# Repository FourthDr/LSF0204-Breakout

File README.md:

LSF0204 Breakout Board
======================

Here are Eagle files for my LSF0204(D) Breakout Board.

<p align="center">
  
</p>

The LSF0204 is a 4-bit, bidirectional, multi-voltage level translator. More info and datasheet here: http://www.ti.com/product/lsf0204

##Features and parts list:

* **U1:** LSF0204(D) IC from Texas Instruments, TSSOP-14 package.
* **C1,C2:** 0.1uF 0805 package. These are decoupling caps.
* **R1-R8:** 4.7k-10k ohm, 0805 package. I2C pull-up resistors for every input/output.
* **R9:** 10k ohm, 0805 package. Pull-down resistor to GND, for LSF0204D: the EN pin is active low.
* **SJ1:** solder jumper to VA, connect for LSF0204 (non-D): the EN pin is active high.

You can visit my website at www.truzzi.me.

Any suggestions or comments are appreciated!

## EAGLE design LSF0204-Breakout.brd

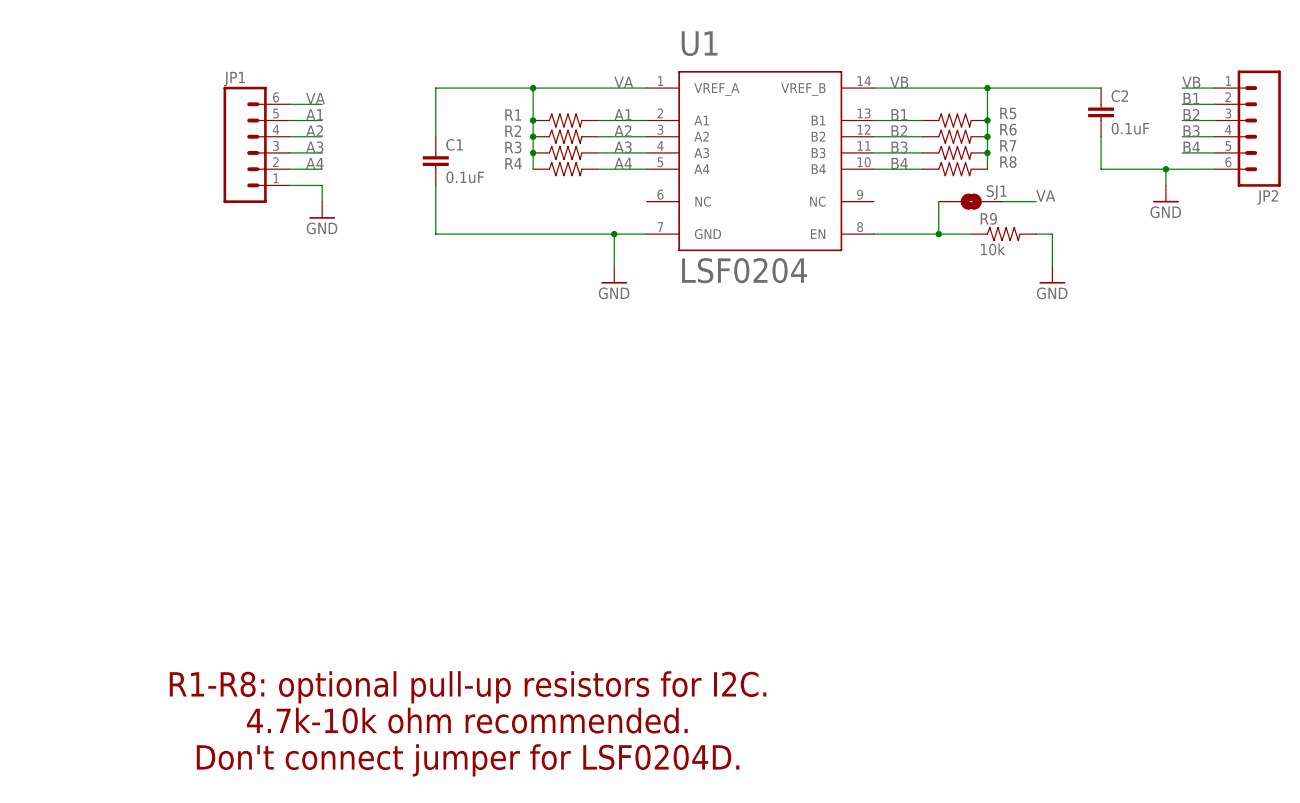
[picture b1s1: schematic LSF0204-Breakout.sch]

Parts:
C1, C2: 0.1uF; 0805
JP1, JP2: M06LOCK; 1X06_LOCK
R1, R2, R3, R4, R5, R6, R7, R8: RESISTOR0805-RES; 0805
R9: 10k; 0805
SJ1: JUMPER-PAD-2-NO; PAD-JUMPER-2-NO_NO_SILK
U1: LSF0204; TSSOP_14

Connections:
A1: JP1.5, R1.2, U1.2 (A1)
A2: JP1.4, R2.2, U1.3 (A2)
A3: JP1.3, R3.2, U1.4 (A3)
A4: JP1.2, R4.2, U1.5 (A4)
B1: JP2.2, R5.1, U1.13 (B1)
B2: JP2.3, R6.1, U1.12 (B2)
B3: JP2.4, R7.1, U1.11 (B3)
B4: JP2.5, R8.1, U1.10 (B4)
GND: C1.2, C2.2, JP1.1, JP2.6, R9.2, U1.7 (GND)
unnamed: R9.1, SJ1.1, U1.8 (EN)
VA: C1.1, JP1.6, R1.1, R2.1, R3.1, R4.1, SJ1.2, U1.1 (VREF_A)
VB: C2.1, JP2.1, R5.2, R6.2, R7.2, R8.2, U1.14 (VREF_B)

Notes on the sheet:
R1-R8: optional pull-up resistors for I2C. 4.7k-10k ohm recommended. Don't connect jumper for LSF0204D.

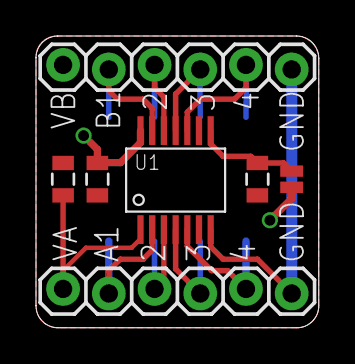
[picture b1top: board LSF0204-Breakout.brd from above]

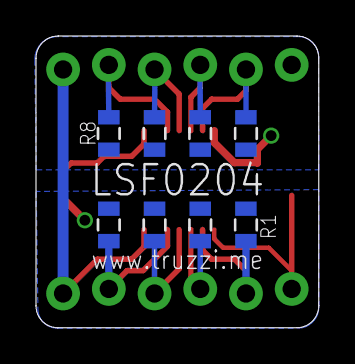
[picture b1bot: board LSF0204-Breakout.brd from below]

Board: 2 copper layers, 15.7 x 16.2 mm, 15 parts (8 on the bottom side), 12 nets.

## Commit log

2015-01-30 :tada: Added .gitattributes & .gitignore files
2015-01-30 Initial release of BRD and SCH files.
2015-01-30 Updated schematics and aesthetics.
2015-01-30 README file created.
2015-01-30 Fixed resistor markings, added image
2015-01-30 New picture

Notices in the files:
LSF0204-Breakout.sch:
LICENSE: Released under CC BY-NC-SA 4.0
parts and their libraries:
SparkFun-Passives: Licensing: Creative Commons ShareAlike 4.0 International - https://creativecommons.org/licenses/by-sa/4.0
